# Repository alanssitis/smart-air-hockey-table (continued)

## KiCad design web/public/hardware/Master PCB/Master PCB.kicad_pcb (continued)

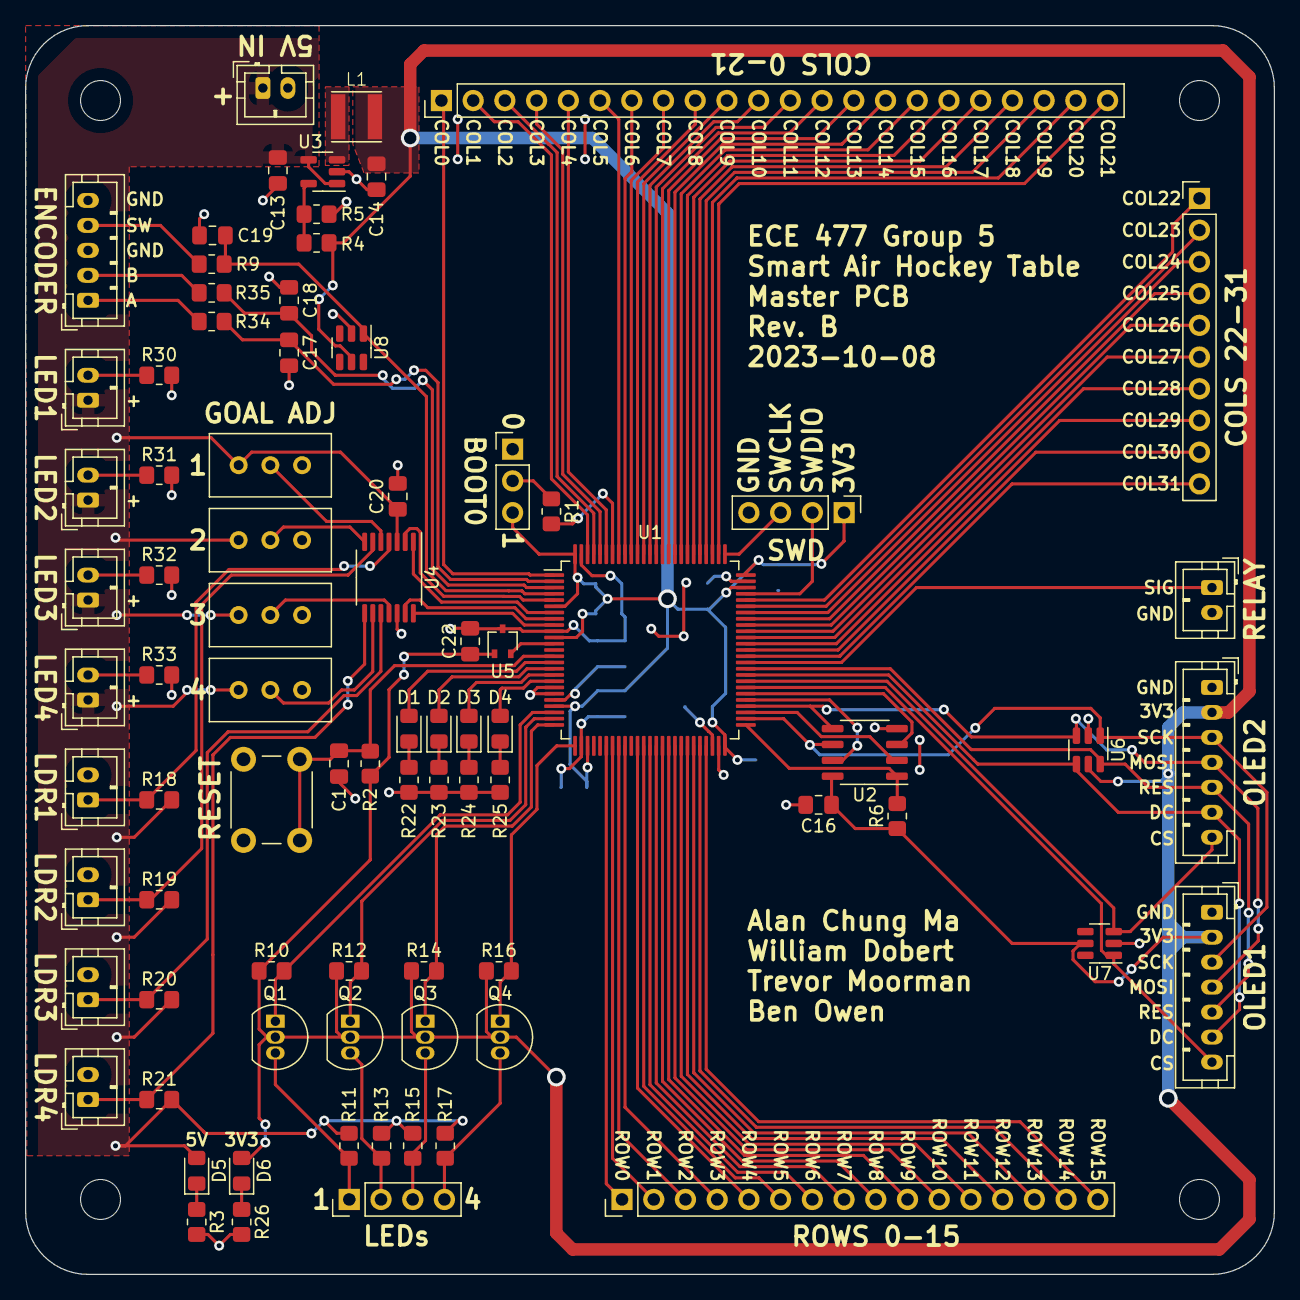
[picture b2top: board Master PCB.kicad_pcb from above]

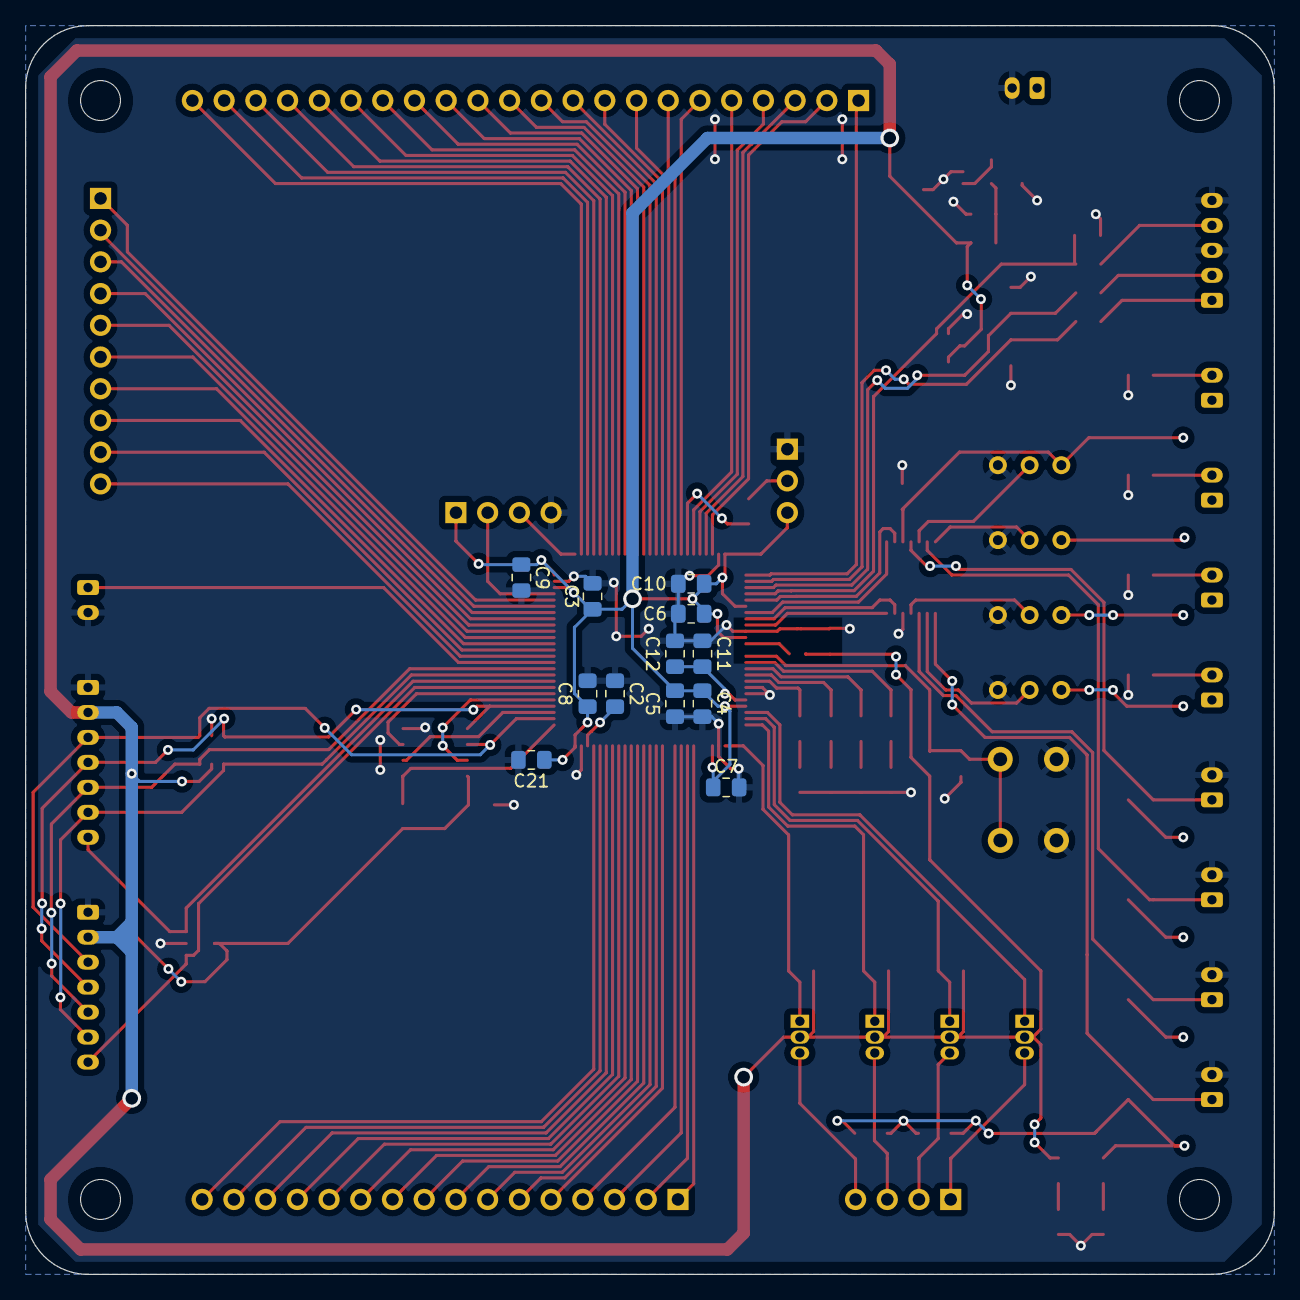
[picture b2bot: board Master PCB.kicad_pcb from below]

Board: 2 copper layers, 100.0 x 100.0 mm, 98 parts (12 on the bottom side), 112 nets.

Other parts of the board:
C21: 100nF; C_0805_2012Metric_Pad1.18x1.45mm_HandSolder
U3: TLV62568DBV; SOT-23-5

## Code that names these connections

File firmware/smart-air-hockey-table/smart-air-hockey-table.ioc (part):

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Mcu.Name=STM32U575VITx
Mcu.Package=LQFP100
Mcu.UserName=STM32U575VITx
PA0.GPIOParameters=GPIO_Label
PA0.GPIO_Label=LED1OUT
PA0.Signal=S_TIM2_CH1
PA1.GPIOParameters=GPIO_Label
PA1.GPIO_Label=LED2OUT
PA1.Signal=S_TIM2_CH2
PA10.GPIOParameters=GPIO_Label
PA10.GPIO_Label=COL24
PA10.Signal=GPIO_Input
PA11.GPIOParameters=GPIO_Label
PA11.GPIO_Label=COL23
PA11.Signal=GPIO_Input
PA12.GPIOParameters=GPIO_Label
PA12.GPIO_Label=COL22
PA12.Signal=GPIO_Input
PA13\ (JTMS/SWDIO).GPIOParameters=GPIO_Label
PA13\ (JTMS/SWDIO).GPIO_Label=SWDIO
PA13\ (JTMS/SWDIO).Mode=Serial_Wire
PA13\ (JTMS/SWDIO).Signal=DEBUG_JTMS-SWDIO
PA14\ (JTCK/SWCLK).GPIOParameters=GPIO_Label
PA14\ (JTCK/SWCLK).GPIO_Label=SWCLK
PA14\ (JTCK/SWCLK).Mode=Serial_Wire
PA14\ (JTCK/SWCLK).Signal=DEBUG_JTCK-SWCLK
PA15\ (JTDI).GPIOParameters=GPIO_Label
PA15\ (JTDI).GPIO_Label=COL21
PA15\ (JTDI).Signal=GPIO_Input
PA2.GPIOParameters=GPIO_Label
PA2.GPIO_Label=LED3OUT
PA2.Signal=S_TIM2_CH3
PA3.GPIOParameters=GPIO_Label
PA3.GPIO_Label=LED4OUT
PA3.Signal=S_TIM2_CH4
PA6.GPIOParameters=GPIO_Label
PA6.GPIO_Label=ROW0
PA6.Signal=GPIO_Input
PA7.GPIOParameters=GPIO_Label
PA7.GPIO_Label=ROW1
PA7.Signal=GPIO_Input
PA8.GPIOParameters=GPIO_Label
PA8.GPIO_Label=COL26
PA8.Signal=GPIO_Input
PA9.GPIOParameters=GPIO_Label
PA9.GPIO_Label=COL25
PA9.Signal=GPIO_Input
PB1.GPIOParameters=GPIO_Label
PB1.GPIO_Label=ROW4
PB1.Signal=GPIO_Input
PB10.GPIOParameters=GPIO_Label
PB10.GPIO_Label=ROW15
PB10.Signal=GPIO_Input
PB12.GPIOParameters=GPIO_Label
PB12.GPIO_Label=MEM1CS
PB12.Signal=GPIO_Output
PB13.GPIOParameters=GPIO_Label
PB13.GPIO_Label=SPI2SCK
PB13.Mode=Full_Duplex_Master
PB13.Signal=SPI2_SCK
PB14.GPIOParameters=GPIO_Label
PB14.GPIO_Label=SPI2MISO
PB14.Mode=Full_Duplex_Master
PB14.Signal=SPI2_MISO
PB15.GPIOParameters=GPIO_Label
PB15.GPIO_Label=SPI2MOSI
PB15.Mode=Full_Duplex_Master
PB15.Signal=SPI2_MOSI
PB2.GPIOParameters=GPIO_Label
PB2.GPIO_Label=ROW5
PB2.Signal=GPIO_Input
PB3\ (JTDO/TRACESWO).GPIOParameters=GPIO_Label
PB3\ (JTDO/TRACESWO).GPIO_Label=COL9
PB3\ (JTDO/TRACESWO).Signal=GPIO_Input
PB4\ (NJTRST).GPIOParameters=GPIO_Label
PB4\ (NJTRST).GPIO_Label=COL8
PB4\ (NJTRST).Signal=GPIO_Input
PB5.GPIOParameters=GPIO_Label
PB5.GPIO_Label=COL7
PB5.Signal=GPIO_Input
PB6.GPIOParameters=GPIO_Label
PB6.GPIO_Label=COL6
PB6.Signal=GPIO_Input
PB7.GPIOParameters=GPIO_Label
PB7.GPIO_Label=COL5
PB7.Signal=GPIO_Input
PB8.GPIOParameters=GPIO_Label
PB8.GPIO_Label=COL4
PB8.Signal=GPIO_Input
PB9.GPIOParameters=GPIO_Label
PB9.GPIO_Label=COL3
PB9.Signal=GPIO_Input
PC0.GPIOParameters=GPIO_Label
PC0.GPIO_Label=DEBUG1
PC0.Signal=GPIO_Output
PC1.GPIOParameters=GPIO_Label
PC1.GPIO_Label=DEBUG2
PC1.Signal=GPIO_Output
PC10.GPIOParameters=GPIO_Label
PC10.GPIO_Label=COL20
PC10.Signal=GPIO_Input
PC11.GPIOParameters=GPIO_Label
PC11.GPIO_Label=COL19
PC11.Signal=GPIO_Input
PC12.GPIOParameters=GPIO_Label
PC12.GPIO_Label=COL18
PC12.Signal=GPIO_Input
PC13.GPIOParameters=GPIO_PuPd,GPIO_Label
PC13.GPIO_Label=LDR2IN
PC13.GPIO_PuPd=GPIO_PULLUP
PC13.Signal=GPIO_Input
PC14-OSC32_IN\ (PC14).GPIOParameters=GPIO_PuPd,GPIO_Label
PC14-OSC32_IN\ (PC14).GPIO_Label=LDR3IN
PC14-OSC32_IN\ (PC14).GPIO_PuPd=GPIO_PULLUP
PC14-OSC32_IN\ (PC14).Signal=GPIO_Input
PC15-OSC32_OUT\ (PC15).GPIOParameters=GPIO_PuPd,GPIO_Label
PC15-OSC32_OUT\ (PC15).GPIO_Label=LDR4IN
PC15-OSC32_OUT\ (PC15).GPIO_PuPd=GPIO_PULLUP
PC15-OSC32_OUT\ (PC15).Signal=GPIO_Input
PC2.GPIOParameters=GPIO_Label
PC2.GPIO_Label=DEBUG3
PC2.Signal=GPIO_Output
PC3.GPIOParameters=GPIO_Label
PC3.GPIO_Label=DEBUG4
PC3.Signal=GPIO_Output
PC4.GPIOParameters=GPIO_Label
PC4.GPIO_Label=ROW2
PC4.Signal=GPIO_Input
PC5.GPIOParameters=GPIO_Label
PC5.GPIO_Label=ROW3
PC5.Signal=GPIO_Input
PC6.GPIOParameters=GPIO_Label
PC6.GPIO_Label=COL30
PC6.Signal=GPIO_Input
PC7.GPIOParameters=GPIO_Label
PC7.GPIO_Label=COL29
PC7.Signal=GPIO_Input
PC8.GPIOParameters=GPIO_Label
PC8.GPIO_Label=COL28
PC8.Signal=GPIO_Input
PC9.GPIOParameters=GPIO_Label
PC9.GPIO_Label=COL27
PC9.Signal=GPIO_Input
PD0.GPIOParameters=GPIO_Label
PD0.GPIO_Label=COL17
PD0.Signal=GPIO_Input
PD1.GPIOParameters=GPIO_Label
PD1.GPIO_Label=COL16
PD1.Signal=GPIO_Input
PD10.GPIOParameters=GPIO_Label
PD10.GPIO_Label=OLED1CS
PD10.Signal=GPIO_Output
PD11.GPIOParameters=GPIO_Label
PD11.GPIO_Label=OLED2CS
PD11.Signal=GPIO_Output
PD12.GPIOParameters=GPIO_Label
PD12.GPIO_Label=OLEDDC
PD12.Signal=GPIO_Output
PD13.GPIOParameters=GPIO_Label
PD13.GPIO_Label=OLEDRES
PD13.Signal=GPIO_Output
PD14.GPIOParameters=GPIO_Label
PD14.GPIO_Label=RELAY
PD14.Signal=GPIO_Output
PD15.GPIOParameters=GPIO_Label
PD15.GPIO_Label=COL31
PD15.Signal=GPIO_Input
PD2.GPIOParameters=GPIO_Label
PD2.GPIO_Label=COL15
PD2.Signal=GPIO_Input
PD3.GPIOParameters=GPIO_Label
PD3.GPIO_Label=COL14
PD3.Signal=GPIO_Input
PD4.GPIOParameters=GPIO_Label
PD4.GPIO_Label=COL13
PD4.Signal=GPIO_Input
PD5.GPIOParameters=GPIO_Label
PD5.GPIO_Label=COL12
PD5.Signal=GPIO_Input
PD6.GPIOParameters=GPIO_Label
PD6.GPIO_Label=COL11
PD6.Signal=GPIO_Input
PD7.GPIOParameters=GPIO_Label
PD7.GPIO_Label=COL10
PD7.Signal=GPIO_Input
PD8.GPIOParameters=GPIO_Label
PD8.GPIO_Label=MEMHOLD
PD8.Signal=GPIO_Output
PD9.GPIOParameters=GPIO_Label
PD9.GPIO_Label=MEMW
PD9.Signal=GPIO_Output
PE0.GPIOParameters=GPIO_Label
PE0.GPIO_Label=COL2
PE0.Signal=GPIO_Input
PE1.GPIOParameters=GPIO_Label
PE1.GPIO_Label=COL1
PE1.Signal=GPIO_Input
PE10.GPIOParameters=GPIO_Label
PE10.GPIO_Label=ROW9
PE10.Signal=GPIO_Input
PE11.GPIOParameters=GPIO_Label
PE11.GPIO_Label=ROW10
PE11.Signal=GPIO_Input
PE12.GPIOParameters=GPIO_Label
PE12.GPIO_Label=ROW11
PE12.Signal=GPIO_Input
PE13.GPIOParameters=GPIO_Label
PE13.GPIO_Label=ROW12
PE13.Signal=GPIO_Input
PE14.GPIOParameters=GPIO_Label
PE14.GPIO_Label=ROW13
PE14.Signal=GPIO_Input
PE15.GPIOParameters=GPIO_Label
PE15.GPIO_Label=ROW14
PE15.Signal=GPIO_Input
PE2.GPIOParameters=GPIO_Label
PE2.GPIO_Label=COL0
PE2.Signal=GPIO_Input
PE3.GPIOParameters=GPIO_PuPd,GPIO_Label
PE3.GPIO_Label=ENCODER_A
PE3.GPIO_PuPd=GPIO_PULLUP
PE3.Signal=S_TIM3_CH1
PE4.GPIOParameters=GPIO_PuPd,GPIO_Label
PE4.GPIO_Label=ENCODER_B
PE4.GPIO_PuPd=GPIO_PULLUP
PE4.Signal=S_TIM3_CH2
PE5.GPIOParameters=GPIO_PuPd,GPIO_Label
PE5.GPIO_Label=ENCODER_SW
PE5.GPIO_PuPd=GPIO_PULLUP
PE5.Signal=GPIO_Input
PE6.GPIOParameters=GPIO_PuPd,GPIO_Label
PE6.GPIO_Label=LDR1IN
PE6.GPIO_PuPd=GPIO_PULLUP
PE6.Signal=GPIO_Input
PE7.GPIOParameters=GPIO_Label
PE7.GPIO_Label=ROW6
PE7.Signal=GPIO_Input
PE8.GPIOParameters=GPIO_Label
PE8.GPIO_Label=ROW7
PE8.Signal=GPIO_Input
PE9.GPIOParameters=GPIO_Label
PE9.GPIO_Label=ROW8
PE9.Signal=GPIO_Input
PH0-OSC_IN\ (PH0).GPIOParameters=GPIO_Label
PH0-OSC_IN\ (PH0).GPIO_Label=OSC_IN
PH0-OSC_IN\ (PH0).Mode=HSE-External-Clock-Source
PH0-OSC_IN\ (PH0).Signal=RCC_OSC_IN
RCC.HSE_VALUE=16000000
RCC.SYSCLKFreq_VALUE=160000000
RCC.SYSCLKSource=RCC_SYSCLKSOURCE_PLLCLK
board=custom

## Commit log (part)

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2023-09-22 Week 5 Progress Report
2023-09-22 Adjustment
2023-09-22 Happy medium
2023-09-22 Add spacers
2023-09-22 update debug for other ST link
2023-09-22 template for week 5 progress alan
2023-09-22 Make schematics larger
2023-09-22 Fixed image sizing
2023-09-22 Added measurement markings to Sensor PCB
2023-09-22 finish alan progress:
2023-09-22 Merge PCB files (#53)
    * Initial commit with some master PCB schematic added
    * Add row/column headers, some hierarchical sheets
    * Add EEPROM
    * Add encoder
    * Add LED level shifters
    * Add goal detection
2023-09-23 Updated to match submission
    Changes formatting of quantities to be "number" instead of "text" in Microsoft Excel
2023-09-26 Add A6 - Mechanical Overview
2023-09-28 Grouped Connectors, LEDs, and Mounting Holes
    Each were group separately
2023-09-29 Connected Hall Effect Sensors to Bus
2023-09-29 Connected AND gates to hall effect output bus
2023-09-29 Bounded AND gate section
2023-09-29 Complete layout without connectors wired
2023-09-29 Wired input connectors
    Connected the outputs of the input connectors to the relevant inputs of the AND gates and LEDs
2023-09-29 Wired LED output to output connector
2023-09-29 Minor changes
    Moved text of some components and minor changes to wiring
2023-09-29 Minor change
2023-09-29 Minor change
    Moved hall effect sensor section up just a little
2023-09-29 Created week 6 progress report
2023-09-29 Adjust image sizing
2023-09-30 Add week 6 progress report
2023-09-30 Week 6
2023-10-01 Upload A8
2023-10-03 Display driver basics
2023-10-03 Change STM32 pinout, begin placing components on new PCB
2023-10-03 Switch JST to THT
2023-10-03 Add ESD ICs and route part of board
2023-10-04 Implement display printing and score tracking
2023-10-04 Finish routing
2023-10-04 Remove locks
2023-10-04 Update labels
2023-10-04 Fix vias
2023-10-04 Update buck converter resistor values
2023-10-04 display is now a bitmask, allow for simultaneous transmit
2023-10-04 Fix if logic
2023-10-04 transmit_end uses bitmask instead of multiple function calls
2023-10-04 Fix encoder resistor values
2023-10-04 Add production files
2023-10-04 Add DRC exclusions
2023-10-04 Updated based on Ben's feedback
    Removed wires between blocks, instead relying on them being connected based on net names (pained me to do this)
    Fixed D3/D4 so they match the PCB layout
    Renamed minor components that were previously unnamed
2023-10-04 Removed gitignore
    Hardware's gitignore will cover these cases after branch is merged
2023-10-05 Remove Sensor PCB .lck file
2023-10-05 Literally add one space
2023-10-05 Make brace style consistent
2023-10-05 Miscellaneous cleanup
2023-10-05 Update indicator LED resistor values
2023-10-05 Schematic cleanup
2023-10-05 Fix Init and make ShowScore more general-purpose
2023-10-05 Shorten power plane along left side of board
2023-10-05 Stitch ground plane under STM32
2023-10-05 Miscellaneous trace cleanup
2023-10-05 DRC exclusion
2023-10-05 Change date and generate production files
2023-10-05 Create new workspaces, default project for each
2023-10-06 Upload generated files
2023-10-06 Add peripherals to Nucleo project, remove unneeded printf stuff
2023-10-06 Remove weird autogen file
2023-10-06 alan week 7 report
2023-10-06 Updated sizing and added hours
2023-10-06 Created week 7 progress report
2023-10-07 Week 7 progress report
2023-10-07 Add images
2023-10-09 Fix encoder schematic and miscellaneous cleanup (new date, etc.)
2023-10-09 More misc. cleanup and generate updated production files
2023-10-09 add picasso painting to home page
2023-10-09 refactor of oled display driver
    moved separator character in score to its own value
    made program print space for unprintable characters
2023-10-09 refactor led write_buffer
2023-10-09 use look-up array for setting to dma_buffer
2023-10-10 Update references for components
2023-10-10 Add master/sensor PCB files
2023-10-10 Update A4
2023-10-10 Add encoder and OLED controller datasheets
2023-10-10 add updated table cad files
    added air hockey table cad and f3d files
2023-10-10 update A3
2023-10-10 update presentation
2023-10-10 Fix video in presentation
2023-10-10 Update Master PCB files (again)
2023-10-10 Update A5
2023-10-10 Add photos/videos
2023-10-10 Fix Alan issue
2023-10-10 Shortened about me
2023-10-11 Configure more pins on Nucleo
2023-10-12 Untested display driver revision, should work
2023-10-12 Update midterm presentation to final form
2023-10-13 Circular works with HAL, doesn't work with LED driver yet
2023-10-13 Mid-fix of LED drivr
2023-10-14 Revert changes from previous 3 commits
2023-10-14 Simpler approach to LED driver DMA, complete but untested
2023-10-15 Functioning LED driver
2023-10-16 Fix display driver SPI
2023-10-16 Increase SPI baud rate, fix ticks_missed, remove Clear from FontTest
2023-10-16 Latest IOC to firmware-pcb
2023-10-16 Re-implemented StateMachine
    Created app_statemachine.c and app_statemachine.h
2023-10-16 Encoder driver with test code, lower SPI baud rate for stability
2023-10-16 Remove test code
2023-10-16 Modified boundary checking
    Blame Will for boundary checking at all
2023-10-17 uint8_t -> bool
2023-10-17 Removed comment
2023-10-17 Created struct containing game info
2023-10-17 Added init function
    Also fixed some errors
2023-10-17 Init as error state
2023-10-17 Combine Tick and PollRotation
2023-10-17 More accurate encoder delta
2023-10-17 Add hall effect driver
2023-10-17 Add relay driver
2023-10-17 Reference new drivers and add some logic
2023-10-17 Extern variables
2023-10-17 Rename states
2023-10-17 Fix case-switch indentation
2023-10-17 0xFF -> DISPLAY_ALL
2023-10-18 Fix wacky delta calculation
2023-10-18 LED driver fix
2023-10-18 Relay driver ;)
2023-10-18 Add JLCPCB assembly files
2023-10-18 I forgor one LED part number
2023-10-18 Add .csv files
2023-10-18 Update drill and grid origin
2023-10-18 As per popular request, remove some italics
2023-10-18 run prettify
    ran npm run prettify
2023-10-18 Implement display power control
2023-10-18 Put it in the header
2023-10-18 Created driver files
2023-10-18 Implement Goal Detection Driver
    Goal detection uses external interrupts to mark if a player scores by setting the correct value in a ScoreState enum.
    This enum can be checked while the game is running to see if a player scored and can switch states accordingly.
    Since goal detection does not switch states, there is no issue with multiple external interrupts on the same goal being raised.
2023-10-19 Commented out relay test lines for future testing
2023-10-19 Pre-merge adjustments
2023-10-19 Abstract GPIO ports
2023-10-19 Move indents
2023-10-19 Make compiler happy with less volatile read/writes
2023-10-20 Week 9 progress report
2023-10-20 Functioning quad-channel LED implementation
2023-10-20 alan week 8 & 9 progress report
2023-10-20 Use more relevant include
2023-10-20 Minor formatting
2023-10-20 Created week 9 progress report
2023-10-20 Add hours
2023-10-20 Removed needless prototype name
    Thanks Will <3
2023-10-20 A couple more comments
2023-10-20 Stub week 8/9
2023-10-20 Move bitmask checking to driver
2023-10-20 Explain the shifts
2023-10-21 Week 8/9
2023-10-21 Fix typo
2023-10-23 dma_buffer -> led_data
2023-10-23 Remove redundant variable
2023-10-24 Fix bit math
2023-10-24 Fixed
    with team :)
2023-10-24 Simplify to equivalent logic
2023-10-25 Remove useless functions from encoder, just poll once to clean the state
2023-10-25 Reorder variables
2023-10-25 Interleave LED channels, enable timer DMA burst
2023-10-26 Prefer fast inttypes, prefer non-volatile, fix a couple braces
2023-10-26 Make "ones place" calculation simpler in score display
2023-10-26 Catch leftover bool assignment
2023-10-26 Remove unneeded parentheses
2023-10-27 Stub week 10, fix broken videos
2023-10-27 alan week 10 progress
2023-10-27 Created week 10 progress report
2023-10-27 Added figures
2023-10-27 Added hours
    Plus a minor rephrase
2023-10-28 Week 10 progress report
2023-10-28 you think I proofread?
2023-10-30 Implement led_state buffer of Color structs, getter function
2023-10-30 Range check on getter inputs
2023-10-30 Whoops, actually return something
2023-10-30 Release target for Nucleo project
2023-10-30 changes from will
2023-10-30 add braces
2023-10-30 Minor optimizations and refactors
    Did not touch driver_halleffect cuz its kinda nasty and I don't have
    tuples in this language :(
2023-10-31 Optimization to `-O2`
2023-11-01 Make naming convetions more consistent and clear
2023-11-01 change to use color struct
2023-11-03 fix typos and removed test code
2023-11-03 remove space differences
2023-11-03 cleanup unused macros
2023-11-03 Test code for safekeeping
2023-11-03 Revert LED matrix interleaving
2023-11-03 Revert "Merge branch 'main' into firmware/quad-channel-led"
    This reverts commit 11b63ec03e9ec65b9039815de165a6a370dde1fd, reversing
    changes made to 7eaf12fe9d19c305d2a6bdd48653b3194d50f7e7.
2023-11-03 Simplify defined constants
2023-11-03 Smarter transfer complete handling
2023-11-04 Created week 11 progress report
2023-11-04 Added hours
2023-11-04 Fixed figure source
2023-11-04 Add spacer CAD files
2023-11-04 Week 11 progress report
2023-11-04 Add mention of acrylic spacers
2023-11-04 Week 11
2023-11-05 Add A10
2023-11-05 Uncomment A10 link
2023-11-05 Add launch configurations, more GPDMA channels for LED driver
2023-11-06 Change LED resistor values
2023-11-07 More tests
2023-11-07 Fix a few hall effect pins, reverse direction of encoder button
2023-11-07 Baud rate to 10 Mbit, bring in halleffect fixes, implement LED matrix test
2023-11-07 Added LDR test
2023-11-07 Revert app_core.c to match nucleo for merging into main
2023-11-07 Remove symbolic link entirely
2023-11-07 Re-ran codegen and caught a missed change
2023-11-10 Add 65mm puck
2023-11-10 Week 12 progress report
2023-11-11 Remove loop in SetColor function
    Use pointer casting to remove loop and get away with 3 stores
2023-11-11 Alan Week 12 Progress Report
    Basically no progress
2023-11-11 Added work on A11
2023-11-11 Resized images
2023-11-11 Will's format fix
2023-11-12 Added A11
2023-11-13 Progress as of 1:00pm 11/13/2023
2023-11-14 Move changes to firmware-pcb
2023-11-16 Progress as of 1:15pm 11/16/2023
2023-11-18 alan progress week 13
2023-11-18 Increase height to 0.5 inches
2023-11-18 Created week 13 progress report
2023-11-18 Added hours
    Also resized image
2023-11-18 Week 13
2023-11-18 Mention user manual
2023-11-19 Add A12
2023-11-27 Tickrate to 250 Hz
2023-11-27 Finalize col and row number
2023-11-29 Update spacers to final version
2023-11-29 some test
2023-11-30 crapppo
2023-11-30 Adding animations
2023-11-30 Full game state machine
2023-11-30 Implement menu in idle state
2023-12-01 Add eeprom driver
    Blood, sweat, and tears
2023-12-01 A little cleanup
2023-12-01 Correct goal detection logic
2023-12-01 shitty trail
2023-12-01 Fix side-effect from merge
2023-12-01 Save variables to EEPROM
2023-12-01 Demo code
2023-12-02 Final Report
2023-12-02 Added Week 14-15 Progress Report
2023-12-02 Fix images
2023-12-02 Week 14-15 progress report
2023-12-03 Remove nucleo folder
2023-12-03 Re-add spacers lol
2023-12-04 Upload 4 more CAD files
2023-12-06 Menu changes and other misc
2023-12-06 Add final presentation documents
2023-12-07 Add header to score display, prints on start state
2023-12-07 Add knob
2023-12-07 Reduce clear LED calls and LED tick calls
2023-12-07 Fix 'Game Score' OLED display
2023-12-07 Removed unused
2023-12-07 Revert "Removed unused"
    This reverts commit c0db7cf6a4637f448fdac7ba7140cfa68eb23a19.
2023-12-07 add random glow
2023-12-07 Clean
2023-12-07 fading
2023-12-07 clear trail on switch
2023-12-07 Add KOTH menu setting
2023-12-07 Win animation
2023-12-08 Added paint mode
2023-12-08 Encoder button fix
2023-12-08 Arrow-shaped score animation
2023-12-08 change name
2023-12-08 Larger magnet
2023-12-09 Restore softlink to hardware folder, add 5 more CAD models, fix documents page
2023-12-09 Make link relative
2023-12-09 Upload A13b
2023-12-21 remove sub-directory and format
2023-12-21 reorder some sections
2023-12-21 change footer to trigger deployment
2023-12-21 update header subtitle
2023-12-21 remove email entry
